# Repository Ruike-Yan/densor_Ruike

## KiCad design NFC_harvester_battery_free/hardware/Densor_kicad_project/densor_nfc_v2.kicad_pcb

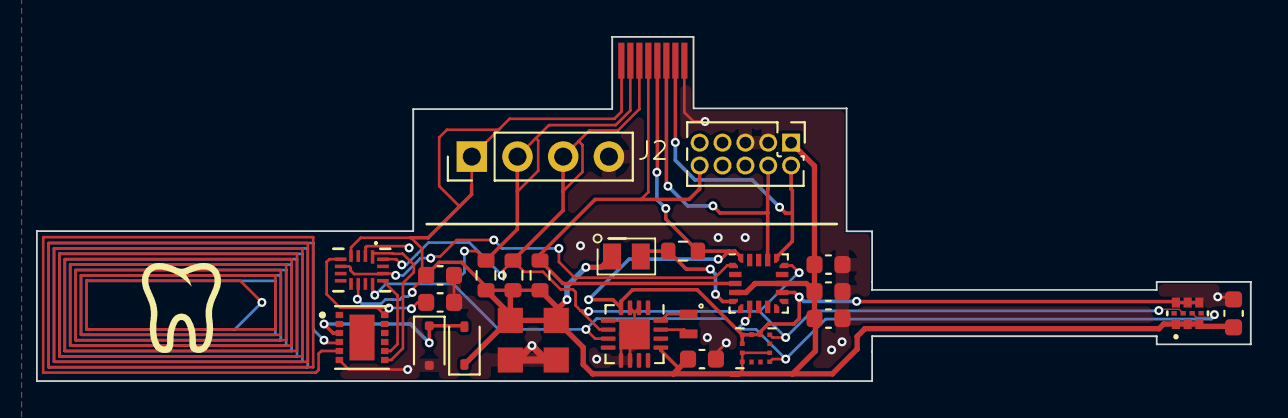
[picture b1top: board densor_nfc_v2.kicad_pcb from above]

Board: 2 copper layers, 67.4 x 19.1 mm, 26 parts (0 on the bottom side), 17 nets.

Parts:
C1, C2: C_Polarized; CPX3225A
C4, C5, C6, C7, C12, C13, C14: 100n; C_0603_1608Metric
D1: D_Zener_3v3; D_SOD-323F
D2: BAS316; D_SOD-323
D3: D_Photo; pd_vemd1060x01
J1: Conn_ARM_JTAG_SWD_10; PinHeader_2x05_P1.27mm_Vertical
J2: Conn_01x08_Pin; fpc_503480-0800
J3: Conn_01x04_Pin; PinHeader_1x04_P2.54mm_Vertical
R2, R3, R4: 100k; R_0603_1608Metric
R7: R; R_0603_1608Metric
U1: ST25DV04K-JFR6D3; PSON50P300X300X60-13N
U2: AM1805; QFN-16-1EP_3x3mm_P0.5mm_EP1.7x1.7mm
U3: MAX30208CLB+; 21-100265_MXM
U4: STM32L011F3Ux; ST_UFQFPN-20_3x3mm_P0.5mm
U5: LIS2DW12; Kionix_LGA-12_2x2mm_P0.5mm_LayoutBorder2x4y
U6: TS3A44159; RSV16
Y1: Crystal; ABS05W_Crystal

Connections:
/AC0: U1.4 (AC0), U1.5 (AC1)
/NFC_SWITCH: U4.1 (PC14), U6.6 (IN3-4), U6.14 (IN1-2)
/PSW: J2.5, R7.2, U2.4 (PSW/nIRQ2), U3.4 (GND), U3.5 (GND), U3.6 (GND), U4.12 (VSS), U4.20 (PB9), U5.5 (NC), U5.6 (GND), U5.7 (RES), U5.8 (GND)
/V_EH: D1.1 (K), D2.2 (A), U1.3 (V_EH)
/V_MCU: C1.1, C2.1, C4.1, C5.2, C6.1, C7.2, C12.2, C14.1, D2.1 (K), D3.1 (K), J1.1 (VTref), J2.1, J3.1, R2.1, R3.1, R4.1, U2.13 (VCC), U3.1 (VDD), U3.2 (VDD), U3.3 (VDD), U4.4 (VDDA), U4.13 (VDD), U5.2 (CS), U5.9 (VDD), U5.10 (VDD_IO), U6.4 (COM3), U6.10 (VCC)
/V_NFC_switched: C13.2, U1.12 (VCC), U6.5 (NC3)
/i2c_scl: J2.2, J3.2, R2.2, U2.7 (SCL), U3.9 (SCL), U4.7 (PA4), U5.1 (SCL), U6.12 (COM1)
/i2c_scl_switched: U1.8 (SCL), U6.13 (NC1)
/i2c_sda: J2.3, J3.3, R3.2, U2.6 (SDA), U3.8 (SDA), U4.15 (PA10), U5.4 (SDA), U6.16 (COM2)
/i2c_sda_switched: U1.7 (SDA), U6.1 (NC2)
/nRST_MCU: J1.10 (~RESET), J2.4, R4.2, U4.3 (NRST)
/pd: D3.2 (A), R7.1, U4.5 (PA0)
/swclk: J1.4 (SWDCLK/TCK), J2.6, U4.17 (PA14)
/swdio: J1.2 (SWDIO/TMS), J2.7, U4.16 (PA13)
GND: C1.2, C2.2, C4.2, C5.1, C6.2, C7.1, C12.1, C13.1, C14.2, D1.2 (A), J1.3 (GND), J1.5 (GND), J2.8, J3.4, U1.6 (VSS), U2.2 (WDI), U2.3 (nEXTR), U2.5 (VBAT), U2.9 (VSS), U2.10 (EXTI), U2.17 (VSS), U6.2 (GND)
unnamed: U2.16 (XI), Y1.1
unnamed: U2.15 (XO), Y1.2
